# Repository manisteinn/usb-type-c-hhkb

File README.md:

USB type C connector board for TMK Alt HHKB board
=================================================

Notice: This project probably won't receive any further updates, hasu now has a <a href="https://geekhack.org/index.php?topic=71517.0">usb-type-c version of his controller board</a> and I don't use my HHKB all that much anymore.

I've added the FreeCAD design files for my related additions to the hhkb-alt-cad directory.
These were made in FreeCAD 0.17 a couple of years ago (never got around to release them until now) but seem to work in the current version. Feel free to submit an issue if needed, it might be a quick fix.

HHKB BT port covers and slide switch cap
========================================
I ordered SLA printed covers and switch caps a few years ago from <a href="https://dirtypcbs.com/store/print3d">DirtySLA</a>.   
See the output/order/combined subdirectory for cost-optimized models (they didn't seem to mind attached duplicates) as well as a FCMacro for cost/volume calculation.

I later did a PCB version of the covers and ordered those from <a href="https://oshpark.com">OSHpark</a>.
Recently I got into resin casting, so after discovering the severe yellowing of the SLA printed parts due to UV exposure I decided to make a mold for the slide switch caps and cast copies of them.

<a href="https://imgur.com/a/O6d0kda">Image gallery</a> with more details.

Software requirements
---------------------
FreeCAD 0.17+ with lattice2 addon (install with tools\>addon manager)
0.16 was used for solid PCB import (pcb workbench), I had issues on 0.17

KiCAD v4+ for PCB covers

CAD comments
------------
Origin is PCB top left corner, top surface.

Rear plate port cutouts (bodies) use lattice2 placements, covers use the x-value of those placements for offset
and can thus be edited in place.

Rear plate height above PCB is the minimum clearance below the upper case ribs, check their location if extending beyond that.
Also check the top PCB clearance if extending them inward.

Switch cover is centered, consider the 2mm symmetrical switch travel.

Parts can't be used directly for lattice2 placements, hence the clones

Resources
---------
<a href="https://www.nkkswitches.com/wp-content/themes/impress-blank/search/inc/part.php?part_no=SS22SDH2">SS22SDH2 switch</a>  
<a href="https://www.bivar.com/category/led-indication/rigid-light-pipes/slp/SLP3-150-100-R">SLP3-150-100-R lightpipe</a>  
<a href="http://www.jae.com/z-en/product_en.cfm?l_code=EN&series_code=DX07&product_number=DX07S024JJ2R1300">DX07S024JJ2R1300 usb-c connector</a>  

License
-------

HHKB controller board models included with hasu's permission

<a href="https://creativecommons.org/publicdomain/zero/1.0/">CC0</a> for all my contributions

Original text
=============

Replaces the Mini-USB connector of a  <a href="https://github.com/tmk/HHKB_controller" target="_blank">tmk HHKB controller board</a> with a usb type C connector (JAE DX07S024JJ2) mounted on a small PCB.
No case modification required, just remove existing connector, clean solder pads and solder this board in place.
CC1 and CC2 have 5.1Kohm pulldown (UFP Rd) in order to be usable by type-C host (DFP) devices. 
See <a href="http://www.usb.org/developers/docs/">specification</a> for details

Kicad origin point is the same as tmk HHKB board (useful for gerber overlay)
Fits rev A-G (tiny overlap on revA C5 footprint), isolate second VUSB pad on F,G
USB-C connector footprint modified for oshpark (they don't support overlapping drill hits), might need changes for other fabricators. 

<a href="https://imgur.com/a/JwNwm">Rev1 image gallery</a>

Changelog
---------
Rev 3
- Added thermal relief to type-c connector pads, solid connection caused soldermask fabrication issues

Rev 2
- Added connector keepout area and filled GND zones connected to connector shield
- Moved vias from under connector to between pad rows
- CC1/CC2 pads marked
- Upper shield mounting holes adjusted, footprint DX07S024JJ2-oshpark-cutpads added to library, original kept for other non-cut boards
- Other small adjustments

Todo
----
- ~~Rev1 failed upper plated slots (needs some trimming to fit the connector), replace with larger TH pads~~
- ~~Place vias between A/B pad rows (middle of rows Y offset: 0.735mm from center of A pads)~~
- ~~Mark CC1/CC2 on R1/R2 pads~~
- Larger version (extended left) with power source switching (qi charging etc)

Notes
-----
git commands for cloning submodules (usb-type-c-kicad-lib, usb-type-c.pretty):

    git clone https://github.com/manisteinn/usb-type-c-hhkb
    cd usb-type-c-hhkb
    git submodule update --init

or

    git clone --recursive https://github.com/manisteinn/usb-type-c-hhkb

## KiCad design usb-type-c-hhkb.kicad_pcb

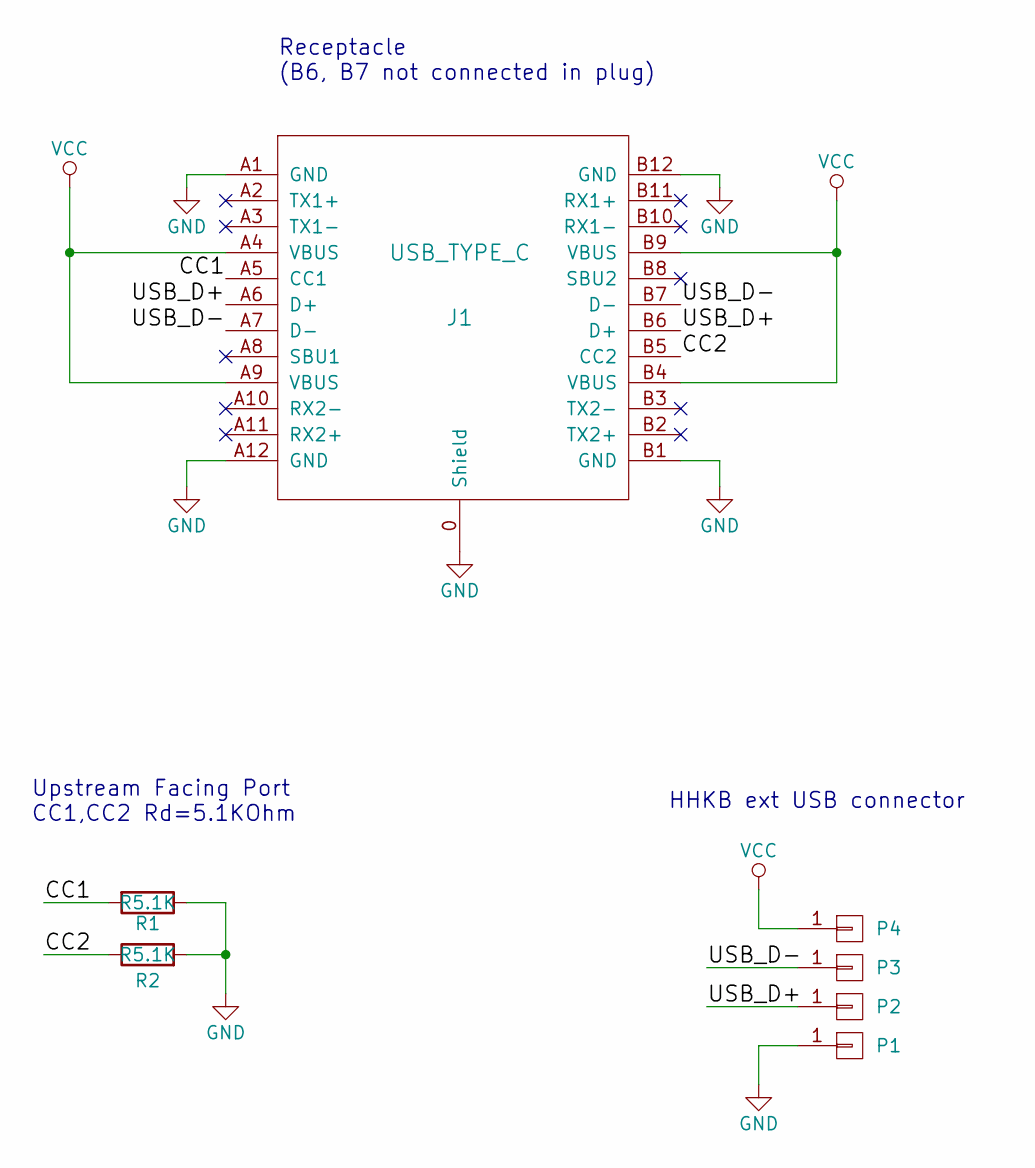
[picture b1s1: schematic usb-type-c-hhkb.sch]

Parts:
J1: USB_TYPE_C; JAE-DX07S024JJ2-oshpark
P1: GND; PIN_1
P2: D+; PIN_1
P3: D-; PIN_1
P4: VCC; PIN_1_SQUARE
R1, R2: R5.1K; R_0603

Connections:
/CC1: J1.A5 (CC1), R1.2
/CC2: J1.B5 (CC2), R2.1
/USB_D+: J1.A6 (D+), J1.B6 (D+), P2.1
/USB_D-: J1.A7 (D-), J1.B7 (D-), P3.1
GND: J1.0 (Shield), J1.A1 (GND), J1.A12 (GND), J1.B1 (GND), J1.B12 (GND), P1.1, R1.1, R2.2
VCC: J1.A4 (VBUS), J1.A9 (VBUS), J1.B4 (VBUS), J1.B9 (VBUS), P4.1

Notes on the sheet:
Receptacle (B6, B7 not connected in plug)
Upstream Facing Port CC1,CC2 Rd=5.1KOhm
HHKB ext USB connector

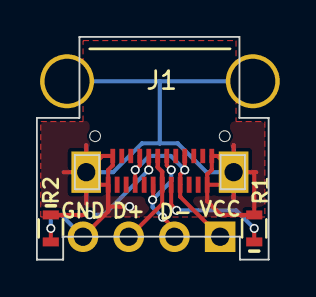
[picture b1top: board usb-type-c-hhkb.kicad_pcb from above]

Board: 2 copper layers, 12.9 x 12.4 mm, 7 parts (0 on the bottom side), 6 nets.

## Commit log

2015-10-09 Rev2
2015-10-12 Library submodule updated (shield pin fix), Rev2 tag moved
2017-04-03 Rev3
2020-01-28 Added CAD files and updated README
